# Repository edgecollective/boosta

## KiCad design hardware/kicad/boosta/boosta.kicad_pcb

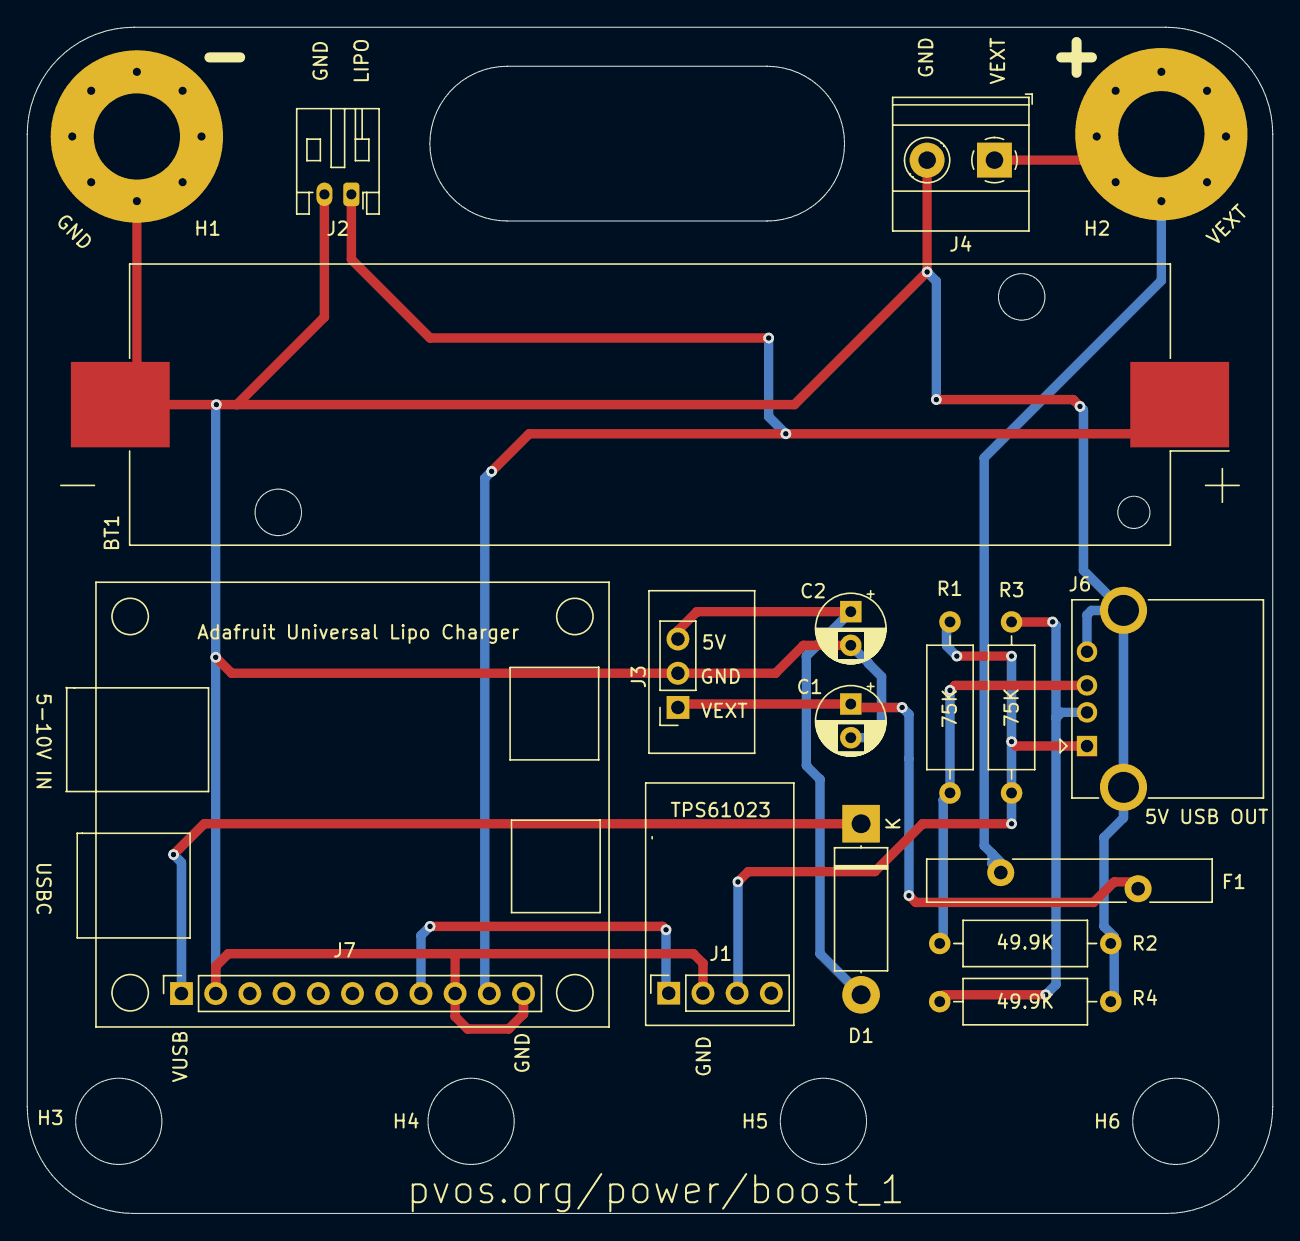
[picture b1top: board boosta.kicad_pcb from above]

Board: 2 copper layers, 92.5 x 88.1 mm, 21 parts (0 on the bottom side), 10 nets.

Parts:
BT1: Battery_Cell; BatteryHolder_Keystone_1042_1x18650
C1: 10uF; CP_Radial_D5.0mm_P2.50mm
C2: 22uF; CP_Radial_D5.0mm_P2.50mm
D1: D; D_5W_P12.70mm_Horizontal
F1: Polyfuse; Fuse_Bourns_MF-RHT1100
H1, H2: MountingHole_Pad; MountingHole_6.4mm_M6_Pad_Via
H3, H4, H5, H6: MountingHole; MountingHole_6.4mm_M6
J1: Conn_01x04_Female; PinSocket_1x04_P2.54mm_Vertical
J2: Conn_01x02_Female; JST_PH_S2B-PH-K_1x02_P2.00mm_Horizontal
J3: Conn_01x03_Female; PinSocket_1x03_P2.54mm_Vertical
J4: Conn_01x02_Female; TerminalBlock_Phoenix_MKDS-1,5-2_1x02_P5.00mm_Horizontal
J6: USB_A; USB_A_CONNFLY_DS1095-WNR0
J7: Conn_01x11_Female; PinSocket_1x11_P2.54mm_Vertical
R1, R3: 75K; R_Axial_DIN0309_L9.0mm_D3.2mm_P12.70mm_Horizontal
R2, R4: 49.9K; R_Axial_DIN0309_L9.0mm_D3.2mm_P12.70mm_Horizontal

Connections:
5VBOOST: J1.3, J6.1, R1.1, R3.2
GND: BT1.2, C1.2, C2.2, H1.1, J1.2, J2.2, J3.2, J4.2, J6.4, J6.5, J7.2, J7.9, J7.11, R2.2, R4.2
LIPO: BT1.1, J2.1, J7.10
unnamed: C1.1, F1.1, J3.1
unnamed: C2.1, D1.2, J3.3
unnamed: F1.2, H2.1, J4.1
unnamed: J6.2, R3.1, R4.1
unnamed: J6.3, R1.2, R2.1
OUT: J1.1, J7.8
VUSB: D1.1, J7.1

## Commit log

2021-10-05 boost_v1 sent to fab
